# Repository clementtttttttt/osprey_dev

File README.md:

# Osprey_dev

ROM and SIO program for the Osprey Portable Computing Unit

ROM contains a graphical operating system 
SIO contains code for handling commands from the cpu

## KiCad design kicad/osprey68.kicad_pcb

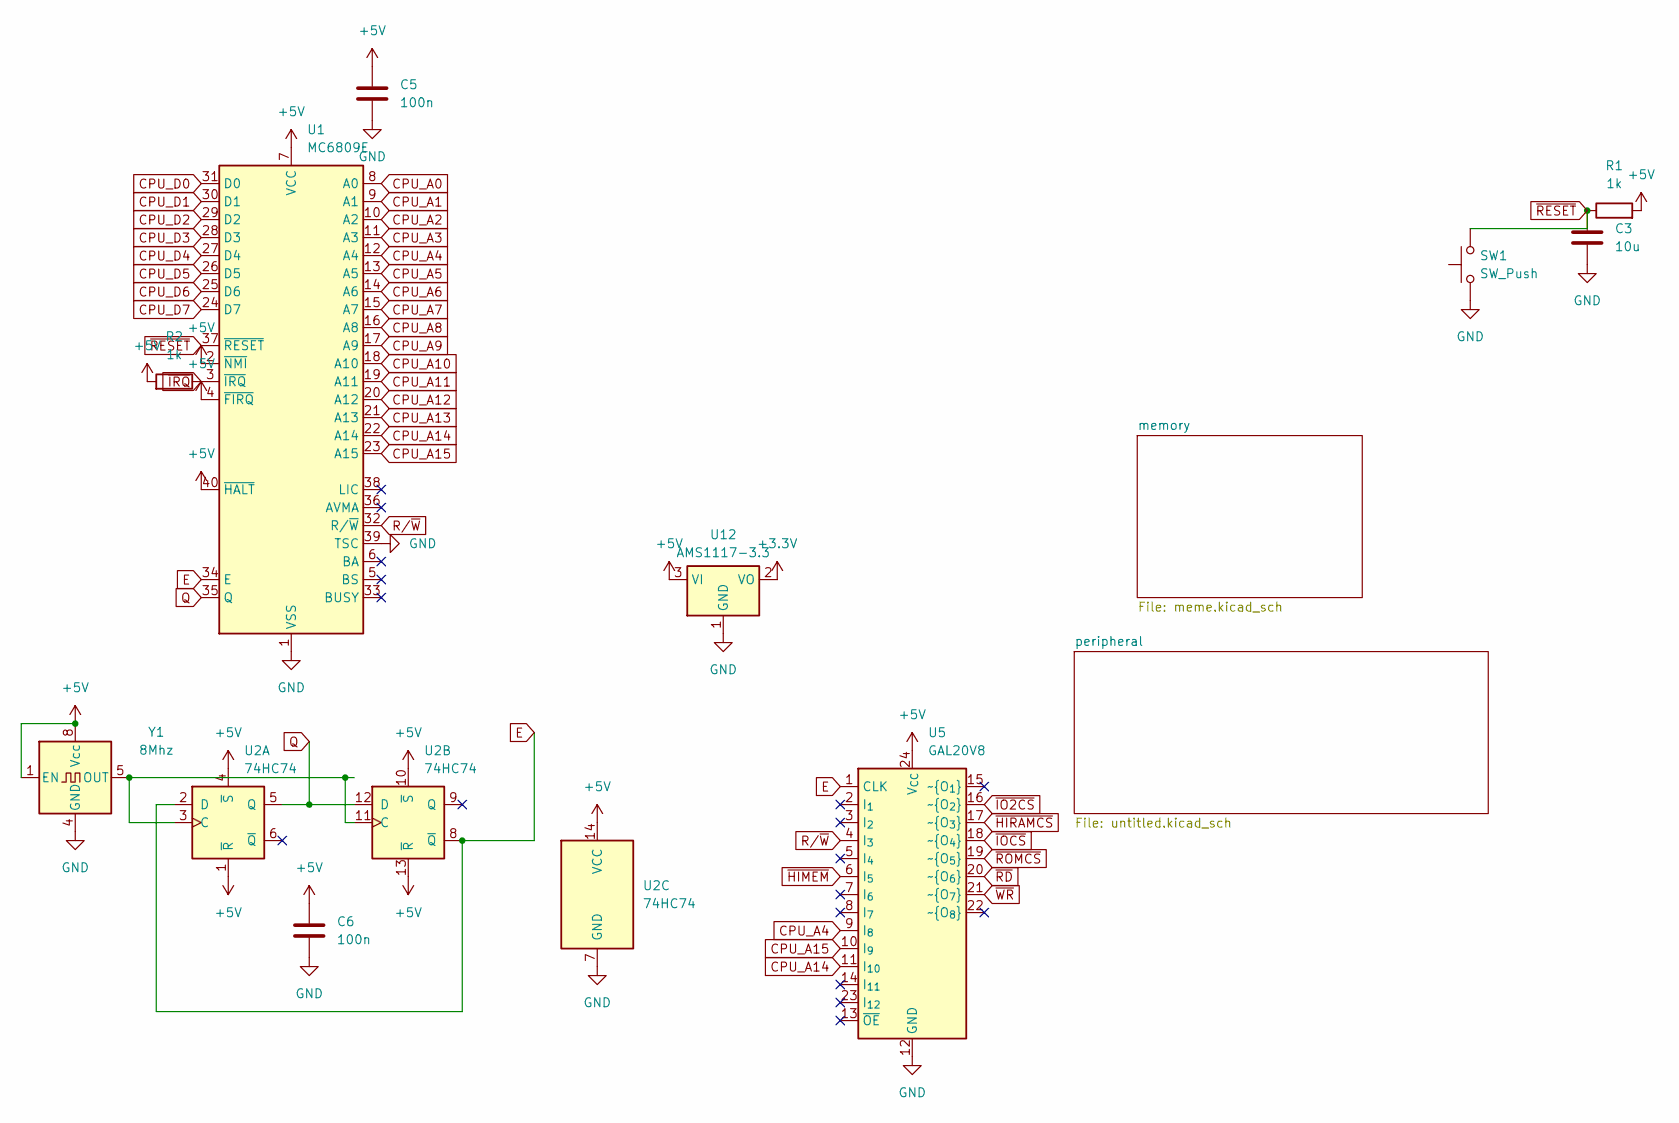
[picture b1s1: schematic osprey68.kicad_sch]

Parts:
C3: 10u; C_0603_1608Metric
C5, C6: 100n; C_0603_1608Metric
R1, R2: 1k; R_0603_1608Metric
SW1: SW_Push; PinHeader_1x02_P2.54mm_Vertical
U1: MC6809E; DIP-40_W15.24mm_Socket
U2: 74HC74; SO-14_3.9x8.65mm_P1.27mm
U5: GAL20V8; DIP-24_W7.62mm_Socket
U12: AMS1117-3.3; SOT-223-3_TabPin2
Y1: 8Mhz; Oscillator_DIP-8

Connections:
+3.3V: U12.2 (VO); also elsewhere on the board
+5V: C5.1, C6.1, R1.2, R2.2, U1.2 (~NMI), U1.4 (~FIRQ), U1.7 (VCC), U1.40 (~HALT), U2.1 (~R), U2.4 (~S), U2.10 (~S), U2.13 (~R), U2.14 (VCC), U5.24 (V_{CC}), U12.3 (VI), Y1.1 (EN), Y1.8 (Vcc); also elsewhere on the board
CPU_A0: U1.8 (A0); also elsewhere on the board
CPU_A1: U1.9 (A1); also elsewhere on the board
CPU_A2: U1.10 (A2); also elsewhere on the board
CPU_A3: U1.11 (A3); also elsewhere on the board
CPU_A4: U1.12 (A4), U5.9 (I_{8}); also elsewhere on the board
CPU_A5: U1.13 (A5); also elsewhere on the board
CPU_A6: U1.14 (A6); also elsewhere on the board
CPU_A7: U1.15 (A7); also elsewhere on the board
CPU_A8: U1.16 (A8); also elsewhere on the board
CPU_A9: U1.17 (A9); also elsewhere on the board
CPU_A10: U1.18 (A10); also elsewhere on the board
CPU_A11: U1.19 (A11); also elsewhere on the board
CPU_A12: U1.20 (A12); also elsewhere on the board
CPU_A13: U1.21 (A13); also elsewhere on the board
CPU_A14: U1.22 (A14), U5.11 (I_{10}); also elsewhere on the board
CPU_A15: U1.23 (A15), U5.10 (I_{9}); also elsewhere on the board
CPU_D0: U1.31 (D0); also elsewhere on the board
CPU_D1: U1.30 (D1); also elsewhere on the board
CPU_D2: U1.29 (D2); also elsewhere on the board
CPU_D3: U1.28 (D3); also elsewhere on the board
CPU_D4: U1.27 (D4); also elsewhere on the board
CPU_D5: U1.26 (D5); also elsewhere on the board
CPU_D6: U1.25 (D6); also elsewhere on the board
CPU_D7: U1.24 (D7); also elsewhere on the board
E: U1.34 (E), U2.2 (D), U2.8 (~Q), U5.1 (CLK); also elsewhere on the board
GND: C3.2, C5.2, C6.2, SW1.1, U1.1 (VSS), U1.39 (TSC), U2.7 (GND), U5.12 (GND), U12.1 (GND), Y1.4 (GND); also elsewhere on the board
unnamed: U2.3 (C), U2.11 (C), Y1.5 (OUT)
Q: U1.35 (Q), U2.5 (Q), U2.12 (D)
R/~W: U1.32 (R/~W), U5.4 (I_{3}); also elsewhere on the board
~HIMEM: U5.6 (I_{5}); also elsewhere on the board
~HIRAMCS: U5.17 (~O_{3}); also elsewhere on the board
~IO2CS: U5.16 (~O_{2}); also elsewhere on the board
~IOCS: U5.18 (~O_{4}); also elsewhere on the board
~IRQ: R2.1, U1.3 (~IRQ); also elsewhere on the board
~RD: U5.20 (~O_{6}); also elsewhere on the board
~RESET: C3.1, R1.1, SW1.2, U1.37 (~RESET); also elsewhere on the board
~ROMCS: U5.19 (~O_{5}); also elsewhere on the board
~WR: U5.21 (~O_{7}); also elsewhere on the board

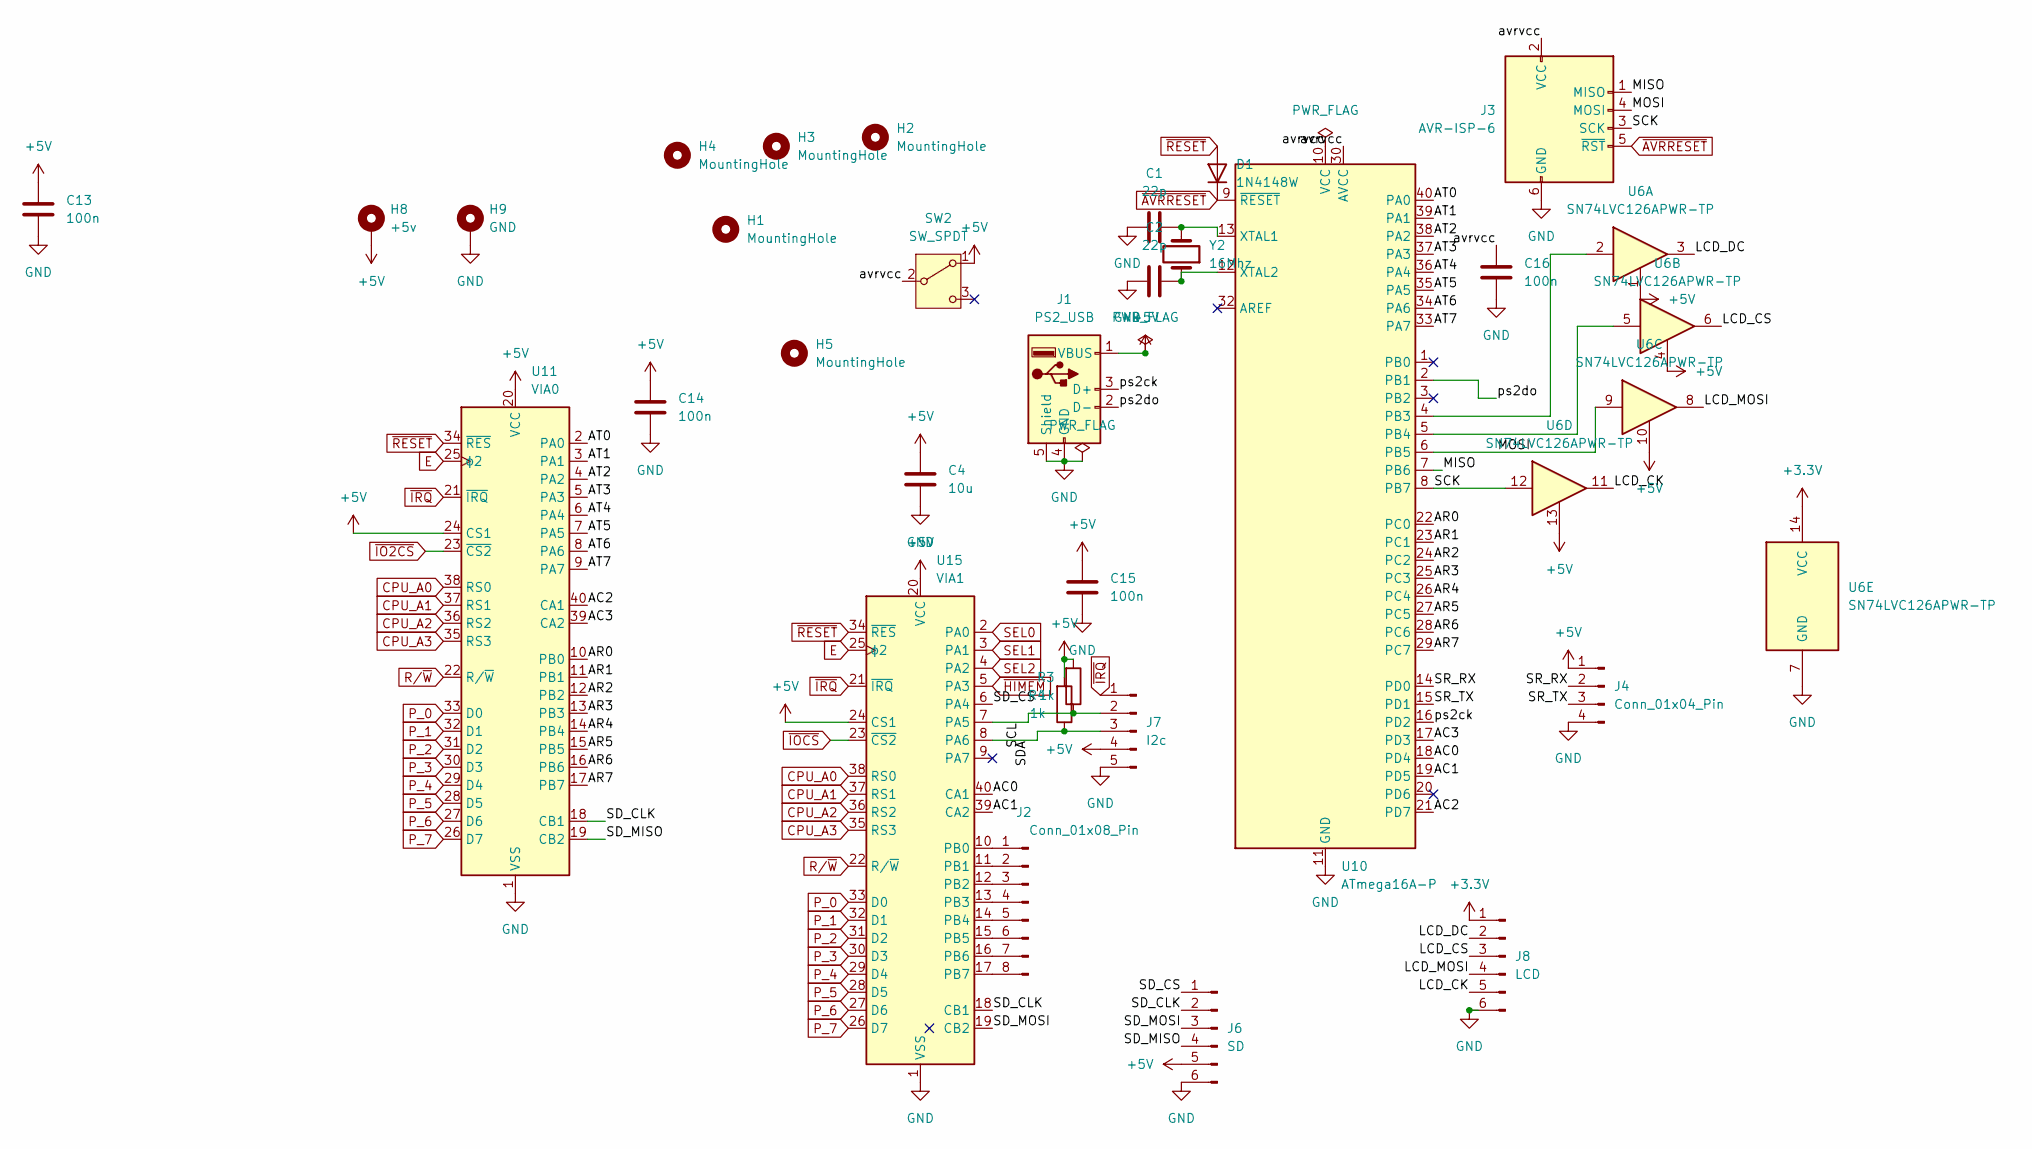
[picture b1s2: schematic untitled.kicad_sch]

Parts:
C1, C2: 22p; C_0603_1608Metric
C4: 10u; C_0603_1608Metric
C13, C14, C15, C16: 100n; C_0603_1608Metric
D1: 1N4148W; D_SOD-123
H1, H2, H3, H4, H5: MountingHole; MountingHole_3.2mm_M3
H8: +5v; MountingHole_2.5mm_Pad_TopBottom
H9: GND; MountingHole_2.5mm_Pad_TopBottom
J1: PS2_USB; USB_A_Molex_67643_Horizontal
J2: Conn_01x08_Pin; PinHeader_1x08_P2.54mm_Vertical
J3: AVR-ISP-6; PinHeader_2x03_P2.54mm_Vertical
J4: Conn_01x04_Pin; PinHeader_1x04_P2.54mm_Vertical
J6: SD; PinHeader_1x06_P2.54mm_Vertical
J7: I2c; PinHeader_1x05_P2.54mm_Vertical
J8: LCD; PinHeader_1x06_P2.54mm_Vertical
R3, R4: 1k; R_0603_1608Metric
SW2: SW_SPDT; PinHeader_1x03_P2.54mm_Vertical
U6: SN74LVC126APWR-TP; TSSOP-14_4.4x5mm_P0.65mm
U10: ATmega16A-P; DIP-40_W15.24mm_Socket
U11: VIA0; DIP-40_W15.24mm_Socket
U15: VIA1; DIP-40_W15.24mm_Socket
Y2: 16Mhz; Crystal_SMD_5032-2Pin_5.0x3.2mm_HandSoldering

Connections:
+3.3V: J8.1, U6.14 (VCC); also elsewhere on the board
+5V: C4.1, C13.1, C14.1, C15.1, H8.1 (1_1), J1.1 (VBUS), J4.1, J6.5, J7.4, R3.2, R4.2, SW2.1 (A), U6.1, U6.4, U6.10, U6.13, U11.20 (VCC), U11.24 (CS1), U15.20 (VCC), U15.24 (CS1); also elsewhere on the board
/peripheral/AC0: U10.18 (PD4), U15.40 (CA1)
/peripheral/AC1: U10.19 (PD5), U15.39 (CA2)
/peripheral/AC2: U10.21 (PD7), U11.40 (CA1)
/peripheral/AC3: U10.17 (PD3), U11.39 (CA2)
/peripheral/AR0: U10.22 (PC0), U11.10 (PB0)
/peripheral/AR1: U10.23 (PC1), U11.11 (PB1)
/peripheral/AR2: U10.24 (PC2), U11.12 (PB2)
/peripheral/AR3: U10.25 (PC3), U11.13 (PB3)
/peripheral/AR4: U10.26 (PC4), U11.14 (PB4)
/peripheral/AR5: U10.27 (PC5), U11.15 (PB5)
/peripheral/AR6: U10.28 (PC6), U11.16 (PB6)
/peripheral/AR7: U10.29 (PC7), U11.17 (PB7)
/peripheral/AT0: U10.40 (PA0), U11.2 (PA0)
/peripheral/AT1: U10.39 (PA1), U11.3 (PA1)
/peripheral/AT2: U10.38 (PA2), U11.4 (PA2)
/peripheral/AT3: U10.37 (PA3), U11.5 (PA3)
/peripheral/AT4: U10.36 (PA4), U11.6 (PA4)
/peripheral/AT5: U10.35 (PA5), U11.7 (PA5)
/peripheral/AT6: U10.34 (PA6), U11.8 (PA6)
/peripheral/AT7: U10.33 (PA7), U11.9 (PA7)
/peripheral/LCD_CK: J8.5, U6.11
/peripheral/LCD_CS: J8.3, U6.6
/peripheral/LCD_DC: J8.2, U6.3
/peripheral/LCD_MOSI: J8.4, U6.8
/peripheral/MISO: J3.1 (MISO), U10.7 (PB6)
/peripheral/MOSI: J3.4 (MOSI), U6.9, U10.6 (PB5)
/peripheral/SCK: J3.3 (SCK), U6.12, U10.8 (PB7)
/peripheral/SCL: J7.2, R3.1, U15.7 (PA5)
/peripheral/SDA: J7.3, R4.1, U15.8 (PA6)
/peripheral/SD_CLK: J6.2, U11.18 (CB1), U15.18 (CB1)
/peripheral/SD_CS: J6.1, U15.6 (PA4)
/peripheral/SD_MISO: J6.4, U11.19 (CB2)
/peripheral/SD_MOSI: J6.3, U15.19 (CB2)
/peripheral/SR_RX: J4.2, U10.14 (PD0)
/peripheral/SR_TX: J4.3, U10.15 (PD1)
/peripheral/avrvcc: C16.1, J3.2 (VCC), SW2.2 (B), U10.10 (VCC), U10.30 (AVCC)
/peripheral/ps2ck: J1.3 (D+), U10.16 (PD2)
/peripheral/ps2do: J1.2 (D-), U10.2 (PB1)
CPU_A0: U11.38 (RS0), U15.38 (RS0); also elsewhere on the board
CPU_A1: U11.37 (RS1), U15.37 (RS1); also elsewhere on the board
CPU_A2: U11.36 (RS2), U15.36 (RS2); also elsewhere on the board
CPU_A3: U11.35 (RS3), U15.35 (RS3); also elsewhere on the board
E: U11.25 (ϕ2), U15.25 (ϕ2); also elsewhere on the board
GND: C1.1, C2.1, C4.2, C13.2, C14.2, C15.2, C16.2, H9.1 (1_1), J1.4 (GND), J1.5 (Shield), J3.6 (GND), J4.4, J6.6, J7.5, J8.6, U6.7 (GND), U10.11 (GND), U10.31 (GND), U11.1 (VSS), U15.1 (VSS); also elsewhere on the board
unnamed: J2.1, U15.10 (PB0)
unnamed: J2.2, U15.11 (PB1)
unnamed: J2.3, U15.12 (PB2)
unnamed: J2.4, U15.13 (PB3)
unnamed: J2.5, U15.14 (PB4)
unnamed: J2.6, U15.15 (PB5)
unnamed: J2.7, U15.16 (PB6)
unnamed: J2.8, U15.17 (PB7)
unnamed: U6.2, U10.4 (PB3)
unnamed: U6.5, U10.5 (PB4)
unnamed: C1.2, U10.13 (XTAL1), Y2.2
unnamed: C2.2, U10.12 (XTAL2), Y2.1
P_0: U11.33 (D0), U15.33 (D0); also elsewhere on the board
P_1: U11.32 (D1), U15.32 (D1); also elsewhere on the board
P_2: U11.31 (D2), U15.31 (D2); also elsewhere on the board
P_3: U11.30 (D3), U15.30 (D3); also elsewhere on the board
P_4: U11.29 (D4), U15.29 (D4); also elsewhere on the board
P_5: U11.28 (D5), U15.28 (D5); also elsewhere on the board
P_6: U11.27 (D6), U15.27 (D6); also elsewhere on the board
P_7: U11.26 (D7), U15.26 (D7); also elsewhere on the board
R/~W: U11.22 (R/~W), U15.22 (R/~W); also elsewhere on the board
SEL0: U15.2 (PA0); also elsewhere on the board
SEL1: U15.3 (PA1); also elsewhere on the board
SEL2: U15.4 (PA2); also elsewhere on the board
~AVRRESET: D1.1 (K), J3.5 (~RST), U10.9 (~RESET)
~HIMEM: U15.5 (PA3); also elsewhere on the board
~IO2CS: U11.23 (~CS2); also elsewhere on the board
~IOCS: U15.23 (~CS2); also elsewhere on the board
~IRQ: J7.1, U11.21 (~IRQ), U15.21 (~IRQ); also elsewhere on the board
~RESET: D1.2 (A), U11.34 (~RES), U15.34 (~RES); also elsewhere on the board

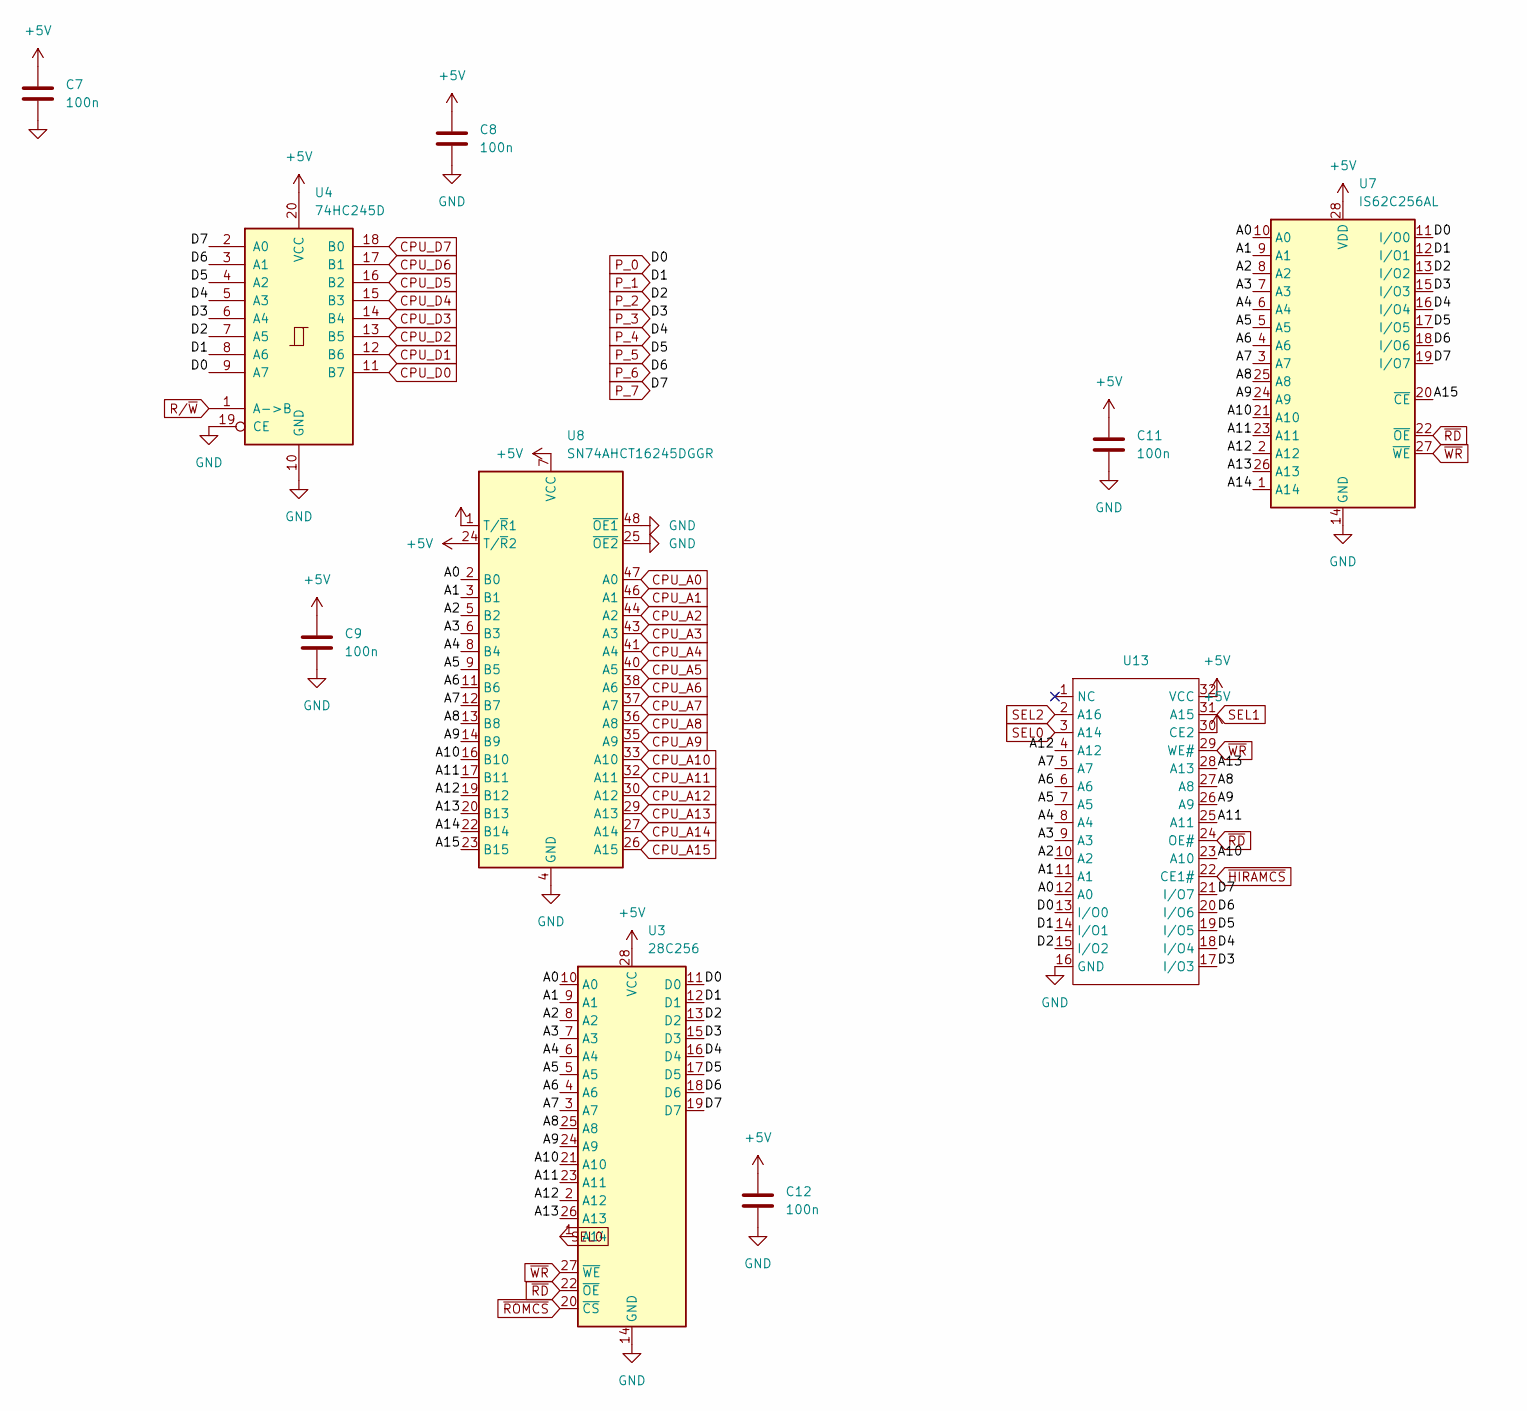
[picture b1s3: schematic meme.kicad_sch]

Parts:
C7, C8, C9, C11, C12: 100n; C_0603_1608Metric
U3: 28C256; DIP_Socket-28_W11.9mm_W12.7mm_W15.24mm_W17.78mm_W18.5mm_3M_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
U4: 74HC245D; SOIC-20W_7.5x12.8mm_P1.27mm
U7: IS62C256AL; SOP-28_8.4x18.16mm_P1.27mm
U8: SN74AHCT16245DGGR; TSSOP-48_6.1x12.5mm_P0.5mm
U13: SOJ-32_7.62x20.955mm_P1.27mm; Manufacturer Part CY7C1009D-10VXIT; LCSC Part Name CY7C1009D 10VXIT

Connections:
+5V: C7.1, C8.1, C9.1, C11.1, C12.1, U3.28 (VCC), U4.20 (VCC), U7.28 (VDD), U8.1 (T/~R1), U8.7 (VCC), U8.18 (VCC), U8.24 (T/~R2), U8.31 (VCC), U8.42 (VCC), U13.30 (CE2), U13.32 (VCC); also elsewhere on the board
/memory/A0: U3.10 (A0), U7.10 (A0), U8.2 (B0), U13.12 (A0)
/memory/A1: U3.9 (A1), U7.9 (A1), U8.3 (B1), U13.11 (A1)
/memory/A2: U3.8 (A2), U7.8 (A2), U8.5 (B2), U13.10 (A2)
/memory/A3: U3.7 (A3), U7.7 (A3), U8.6 (B3), U13.9 (A3)
/memory/A4: U3.6 (A4), U7.6 (A4), U8.8 (B4), U13.8 (A4)
/memory/A5: U3.5 (A5), U7.5 (A5), U8.9 (B5), U13.7 (A5)
/memory/A6: U3.4 (A6), U7.4 (A6), U8.11 (B6), U13.6 (A6)
/memory/A7: U3.3 (A7), U7.3 (A7), U8.12 (B7), U13.5 (A7)
/memory/A8: U3.25 (A8), U7.25 (A8), U8.13 (B8), U13.27 (A8)
/memory/A9: U3.24 (A9), U7.24 (A9), U8.14 (B9), U13.26 (A9)
/memory/A10: U3.21 (A10), U7.21 (A10), U8.16 (B10), U13.23 (A10)
/memory/A11: U3.23 (A11), U7.23 (A11), U8.17 (B11), U13.25 (A11)
/memory/A12: U3.2 (A12), U7.2 (A12), U8.19 (B12), U13.4 (A12)
/memory/A13: U3.26 (A13), U7.26 (A13), U8.20 (B13), U13.28 (A13)
/memory/A14: U7.1 (A14), U8.22 (B14)
/memory/A15: U7.20 (~CE), U8.23 (B15)
CPU_A0: U8.47 (A0); also elsewhere on the board
CPU_A1: U8.46 (A1); also elsewhere on the board
CPU_A2: U8.44 (A2); also elsewhere on the board
CPU_A3: U8.43 (A3); also elsewhere on the board
CPU_A4: U8.41 (A4); also elsewhere on the board
CPU_A5: U8.40 (A5); also elsewhere on the board
CPU_A6: U8.38 (A6); also elsewhere on the board
CPU_A7: U8.37 (A7); also elsewhere on the board
CPU_A8: U8.36 (A8); also elsewhere on the board
CPU_A9: U8.35 (A9); also elsewhere on the board
CPU_A10: U8.33 (A10); also elsewhere on the board
CPU_A11: U8.32 (A11); also elsewhere on the board
CPU_A12: U8.30 (A12); also elsewhere on the board
CPU_A13: U8.29 (A13); also elsewhere on the board
CPU_A14: U8.27 (A14); also elsewhere on the board
CPU_A15: U8.26 (A15); also elsewhere on the board
CPU_D0: U4.11 (B7); also elsewhere on the board
CPU_D1: U4.12 (B6); also elsewhere on the board
CPU_D2: U4.13 (B5); also elsewhere on the board
CPU_D3: U4.14 (B4); also elsewhere on the board
CPU_D4: U4.15 (B3); also elsewhere on the board
CPU_D5: U4.16 (B2); also elsewhere on the board
CPU_D6: U4.17 (B1); also elsewhere on the board
CPU_D7: U4.18 (B0); also elsewhere on the board
GND: C7.2, C8.2, C9.2, C11.2, C12.2, U3.14 (GND), U4.10 (GND), U4.19 (CE), U7.14 (GND), U8.4 (GND), U8.10 (GND), U8.15 (GND), U8.21 (GND), U8.25 (~OE2), U8.28 (GND), U8.34 (GND), U8.39 (GND), U8.45 (GND), U8.48 (~OE1), U13.16 (GND); also elsewhere on the board
P_0: U3.11 (D0), U4.9 (A7), U7.11 (I/O0), U13.13 (I/O0); also elsewhere on the board
P_1: U3.12 (D1), U4.8 (A6), U7.12 (I/O1), U13.14 (I/O1); also elsewhere on the board
P_2: U3.13 (D2), U4.7 (A5), U7.13 (I/O2), U13.15 (I/O2); also elsewhere on the board
P_3: U3.15 (D3), U4.6 (A4), U7.15 (I/O3), U13.17 (I/O3); also elsewhere on the board
P_4: U3.16 (D4), U4.5 (A3), U7.16 (I/O4), U13.18 (I/O4); also elsewhere on the board
P_5: U3.17 (D5), U4.4 (A2), U7.17 (I/O5), U13.19 (I/O5); also elsewhere on the board
P_6: U3.18 (D6), U4.3 (A1), U7.18 (I/O6), U13.20 (I/O6); also elsewhere on the board
P_7: U3.19 (D7), U4.2 (A0), U7.19 (I/O7), U13.21 (I/O7); also elsewhere on the board
R/~W: U4.1 (A->B); also elsewhere on the board
SEL0: U3.1 (A14), U13.3 (A14); also elsewhere on the board
SEL1: U13.31 (A15); also elsewhere on the board
SEL2: U13.2 (A16); also elsewhere on the board
~HIRAMCS: U13.22 (CE1#); also elsewhere on the board
~RD: U3.22 (~OE), U7.22 (~OE), U13.24 (OE#); also elsewhere on the board
~ROMCS: U3.20 (~CS); also elsewhere on the board
~WR: U3.27 (~WE), U7.27 (~WE), U13.29 (WE#); also elsewhere on the board

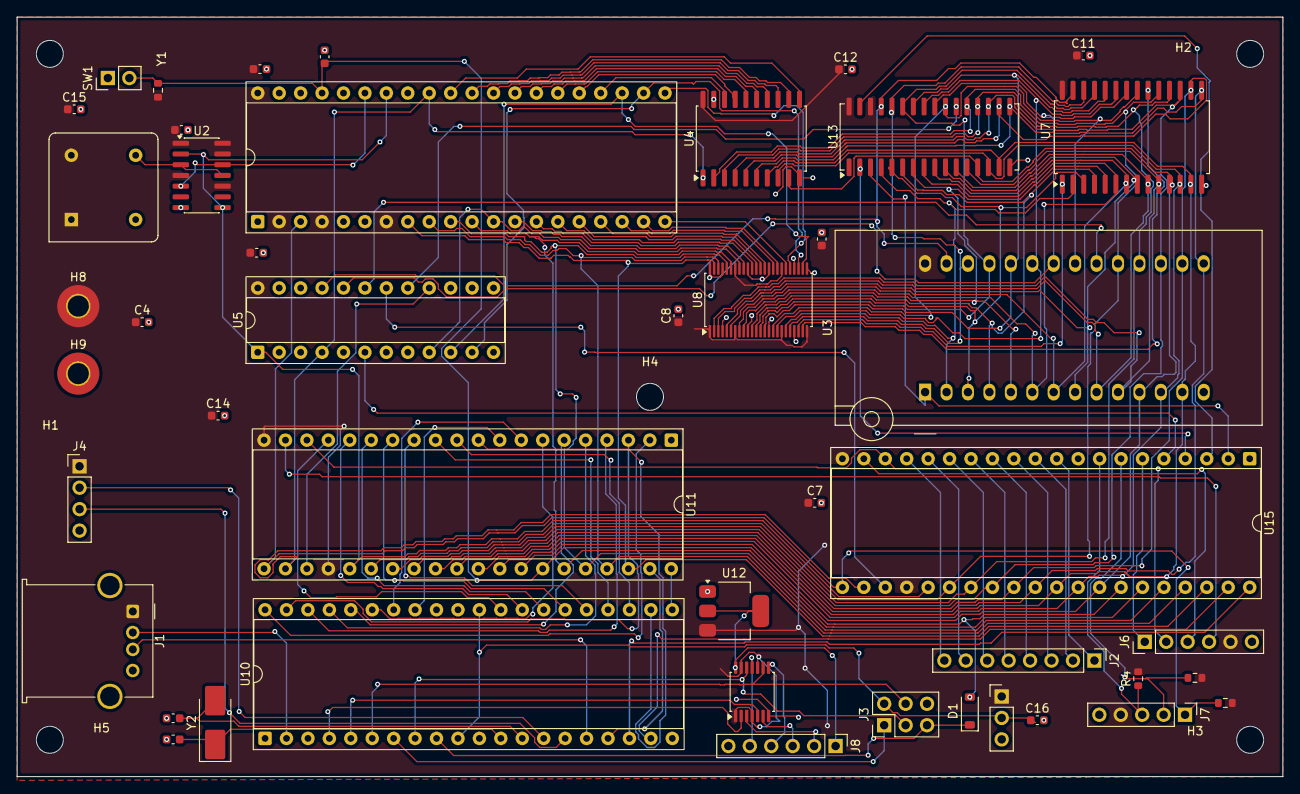
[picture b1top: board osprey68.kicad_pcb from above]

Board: 2 copper layers, 150.0 x 90.0 mm, 51 parts (0 on the bottom side), 118 nets.

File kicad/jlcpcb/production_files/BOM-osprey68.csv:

Comment,Designator,Footprint,LCSC,Quantity
100n,"C11,C12,C13,C14,C15,C16,C5,C6,C7,C8,C9",C_0603_1608Metric,C14663,11
10u,C4,C_0603_1608Metric,C19702,1
10u,C3,C_0603_1608Metric,C96446,1
16Mhz,Y2,Crystal_SMD_5032-2Pin_5.0x3.2mm_HandSoldering,C112572,1
1N4148W,D1,D_SOD-123,C81598,1
1k,"R1,R2,R3,R4",R_0603_1608Metric,C21190,4
22p,"C1,C2",C_0603_1608Metric,C1653,2
74HC245D,U4,SOIC-20W_7.5x12.8mm_P1.27mm,C5625,1
74HC74,U2,SO-14_3.9x8.65mm_P1.27mm,C41361407,1
AMS1117-3.3,U12,SOT-223-3_TabPin2,C6186,1
SN74LVC126APWR-TP,U6,TSSOP-14_4.4x5mm_P0.65mm,C54561942,1
8Mhz,Y1,Oscillator_DIP-8,,1
VIA1,U15,DIP-40_W15.24mm_Socket,,1
VIA0,U11,DIP-40_W15.24mm_Socket,,1
ATmega16A-P,U10,DIP-40_W15.24mm_Socket,,1
128k sram,U9,SOJ-32_7.62x20.955mm_P1.27mm,,1
GAL20V8,U5,DIP-24_W7.62mm_Socket,,1
MC6809E,U1,DIP-40_W15.24mm_Socket,,1
PS2_USB,J1,USB_A_Molex_67643_Horizontal,,1
28C256,U3,DIP_Socket-28_W11.9mm_W12.7mm_W15.24mm_W17.78mm_W18.5mm_3M_228-1277-00-0602J,,1
Conn_01x08_Pin,J2,PinHeader_1x08_P2.54mm_Vertical,,1
SN74AHCT16245DGGR,U8,TSSOP-48_6.1x12.5mm_P0.5mm,,1
SW_Push,SW1,PinHeader_1x02_P2.54mm_Vertical,,1
SW_SPDT,SW2,PinHeader_1x03_P2.54mm_Vertical,,1
AVR-ISP-6,J3,PinHeader_2x03_P2.54mm_Vertical,,1
Conn_01x04_Pin,J4,PinHeader_1x04_P2.54mm_Vertical,,1
SD,J6,PinHeader_1x06_P2.54mm_Vertical,,1
LCD,J8,PinHeader_1x06_P2.54mm_Vertical,,1
I2c,J7,PinHeader_1x05_P2.54mm_Vertical,,1
IS62C256AL,U7,SOP-28_8.4x18.16mm_P1.27mm,,1

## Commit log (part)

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2025-06-21 add everything
2025-06-21 add readme
2025-07-02 avr core 90% complete for emu
2025-07-02 Test
2025-08-18 add PAL files and new source files
2025-08-18 fix readme in 6809 folder
2025-08-22 gui framework: added toolbar and menu
2025-08-22 toolbar & menu draw works
2025-10-04 implemented 6522 timer setup and interrupts
2025-10-06 gui fixes
2025-10-07 add missing files
2025-11-22 added fat routine to read cluster
2025-11-24 implemented more instructions
2026-05-02 convert buildsystem to cmake
2026-05-02 implement 6809 cpu core
2026-05-02 add missing build system files
2026-05-03 move system to meson, major cleanup
2026-05-03 remove obj
2026-05-03 add 6522 code
2026-05-03 add kicad porject
2026-05-03 add ifr cleaning to 6522
2026-05-03 add via decaration to emu
2026-05-06 add spi hook, add 6522 io hook
2026-05-06 fix sd_wait_spi inverted branch, implement ifr reading in 6522
2026-05-06 implement more register reading and writing logic, implement external periphearl interfafce methods and enum for IFr bits
2026-05-06 add method to set ifr_ca1
2026-05-07 connect 6522 to simavr
2026-05-08 sio interface 6522>sio officially working
2026-05-08 added ili9488 module
2026-05-08 scale window to 2x, add hardware interrupt to CPU6809
2026-05-08 hooked irq to 6809
2026-05-08 add ps2kb class and connect via0
2026-05-08 add stdio to uart output
2026-05-08 add adavnced edge detection in ca1 6522
2026-05-08 add cycle counting to 6809 core
2026-05-08 input now wokring for mysterious reasns
2026-05-08 input values sent correctly
2026-05-09 fixed rol bug and added memory inspector, wozmon fully functional
2026-05-09 vscroll working
2026-05-09 fix scancode table
2026-05-09 kb semi owrking
2026-05-09 ps2 keyboard fully working
2026-05-09 change sio firwmare so that it doesnt give char when released in getc, add test in emu
2026-05-10 fix multi gui menu drawing
2026-05-10 optimised ili9488 flush
2026-05-10 remove cpu debug and add back 6809 int dbg msg
2026-05-10 add missing 6522 reg read code
2026-05-10 add cases for reg write 6522
2026-05-10 properly add vsync to limit framerate, add t2 reg write cases
2026-05-10 add memory randomiser
2026-05-10 add good error message for rom and sio reading errors
2026-05-11 remove unused headers
2026-05-11 change cycle_cost to c++ array
2026-05-11 move to sdl3
